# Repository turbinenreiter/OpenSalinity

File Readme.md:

# OpenSalinity

doc - Latex files for the semester thesis  
src - source code  
data - all data gathered during experiments  
hardware - hardware design files  

## Software

The software for the microcontroller is developed using [MicroPython](micropython.org). The controller has to be flashed with the MicroPython firmware before it is able to run the Python scripts. Those Python scripts can be deployed on the microcontroller by copying them over to its filesystem which is present as flash drive when connected to a PC.  

The OpenSalinityGUI offers a simple user interface to capture and visualize data.  

The OpenSalintyCLI shell script uses standard command line tools to do the same.  

DataPlot contains Python scripts to plot and analyze the gathered data.  
All software is licensed under the MIT-license.

## Hardware

In this project, the [Espruino Pico](espruino.com) development board was used, but other boards running MicroPython can replace it.  

Design files for the [MinieC](sparkyswidgets.com) and carrier board files are provided in the [eagle](cadsoft.io)-format.  

Gerbers for the electrode design are offerd as well.  
All hardware is licensed as CC-BY-SA-4.0

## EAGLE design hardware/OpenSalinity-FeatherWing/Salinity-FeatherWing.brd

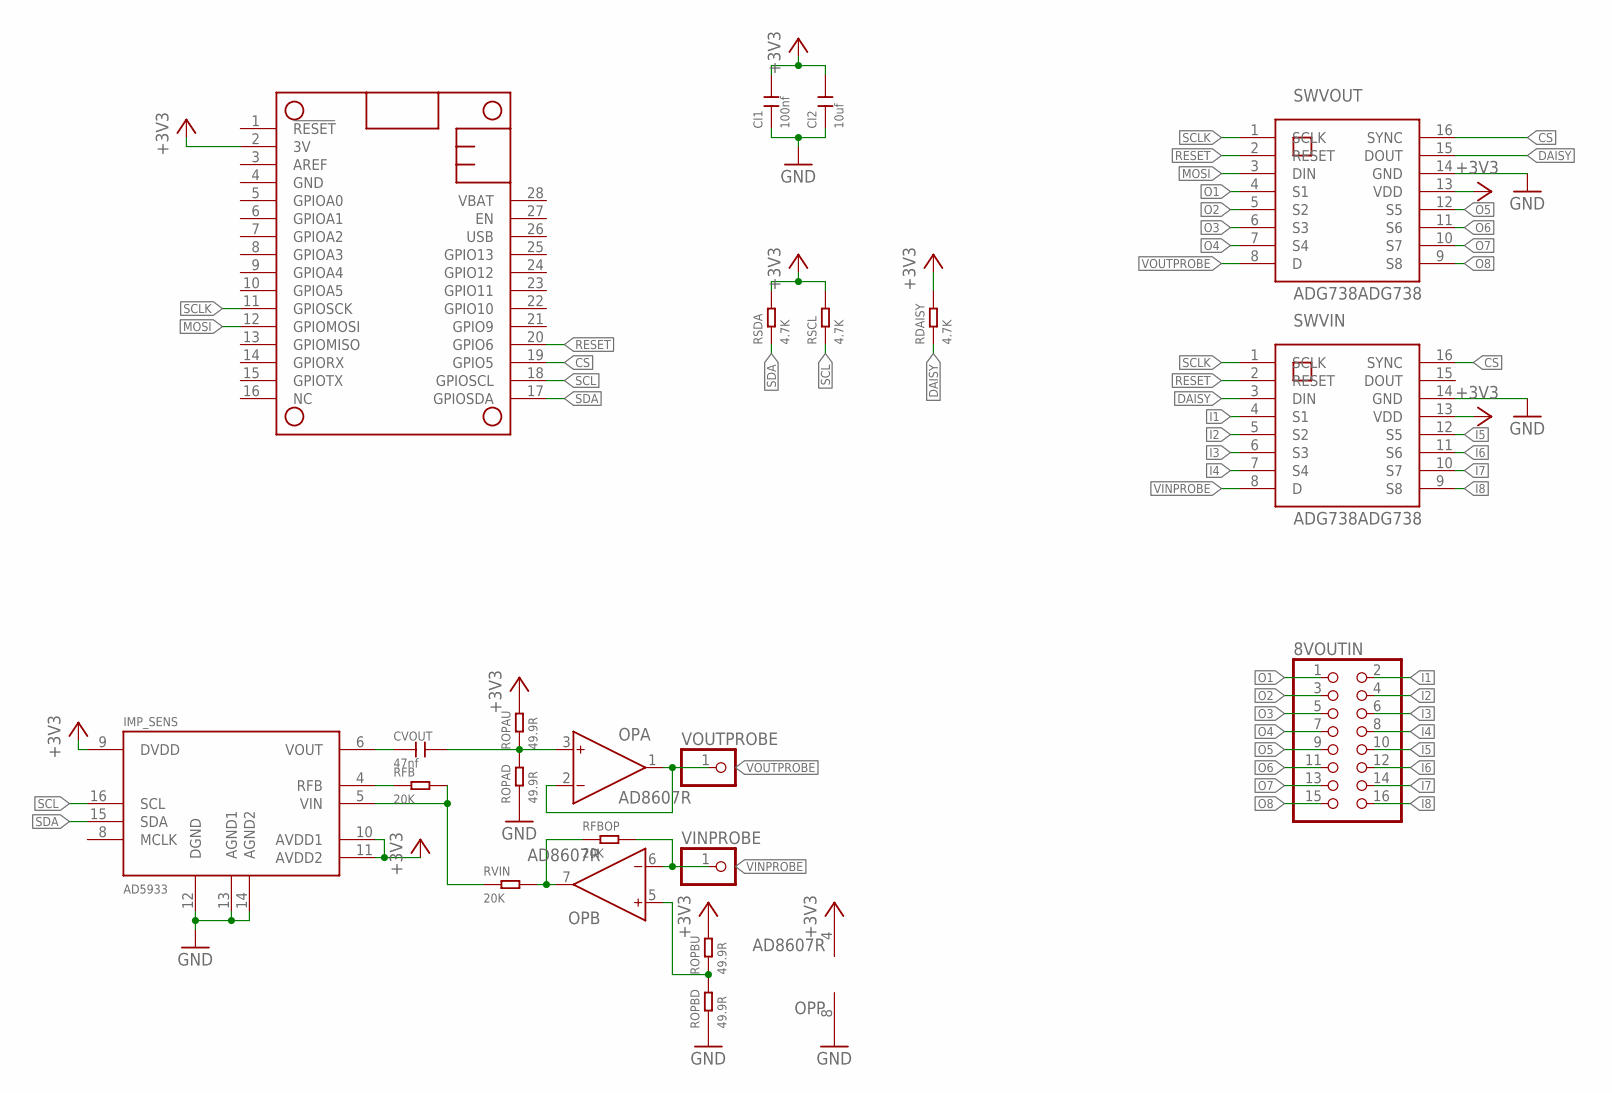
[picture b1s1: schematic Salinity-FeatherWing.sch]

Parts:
8VOUTIN: PINHD-2X8/90; 2X08/90
CI1: 100nf; C0603
CI2: 10uf; C0603
CVOUT: 47nf; C0402
IMP_SENS: AD5933; SSOP16
MS1: FEATHERWING
OP: AD8607R; SO8
RDAISY: 4.7K; R0603
RFB: 20K; R0603
RFBOP: 20K; R0603
ROPAD: 49.9R; R0603
ROPAU: 49.9R; R0603
ROPBD: 49.9R; R0603
ROPBU: 49.9R; R0603
RSCL: 4.7K; R0603
RSDA: 4.7K; R0603
RVIN: 20K; R0603
SWVIN: ADG738ADG738; TSSOP16
SWVOUT: ADG738ADG738; TSSOP16
VINPROBE: PINHD-1X1; 1X01
VOUTPROBE: PINHD-1X1; 1X01

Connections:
+3V3: CI1.2, CI2.2, IMP_SENS.9 (DVDD), IMP_SENS.10 (AVDD1), IMP_SENS.11 (AVDD2), MS1.2 (3V), OP.4 (V-), RDAISY.2, ROPAU.2, ROPBU.2, RSCL.2, RSDA.2, SWVIN.13 (VDD), SWVOUT.13 (VDD)
CS: MS1.19 (GPIO5), SWVIN.16 (SYNC), SWVOUT.16 (SYNC)
DAISY: RDAISY.1, SWVIN.3 (DIN), SWVOUT.15 (DOUT)
GND: CI1.1, CI2.1, IMP_SENS.12 (DGND), IMP_SENS.13 (AGND1), IMP_SENS.14 (AGND2), MS1.4 (GND), OP.8 (V+), ROPAD.1, ROPBD.1, SWVIN.14 (GND), SWVOUT.14 (GND)
I1: 8VOUTIN.2, SWVIN.4 (S1)
I2: 8VOUTIN.4, SWVIN.5 (S2)
I3: 8VOUTIN.6, SWVIN.6 (S3)
I4: 8VOUTIN.8, SWVIN.7 (S4)
I5: 8VOUTIN.10, SWVIN.12 (S5)
I6: 8VOUTIN.12, SWVIN.11 (S6)
I7: 8VOUTIN.14, SWVIN.10 (S7)
I8: 8VOUTIN.16, SWVIN.9 (S8)
MOSI: MS1.12 (GPIOMOSI), SWVOUT.3 (DIN)
unnamed: OP.7 (OUT), RFBOP.1, RVIN.2
unnamed: IMP_SENS.4 (RFB), RFB.1
unnamed: IMP_SENS.5 (VIN), RFB.2, RVIN.1
unnamed: CVOUT.1, IMP_SENS.6 (VOUT)
O1: 8VOUTIN.1, SWVOUT.4 (S1)
O2: 8VOUTIN.3, SWVOUT.5 (S2)
O3: 8VOUTIN.5, SWVOUT.6 (S3)
O4: 8VOUTIN.7, SWVOUT.7 (S4)
O5: 8VOUTIN.9, SWVOUT.12 (S5)
O6: 8VOUTIN.11, SWVOUT.11 (S6)
O7: 8VOUTIN.13, SWVOUT.10 (S7)
O8: 8VOUTIN.15, SWVOUT.9 (S8)
OPA+: CVOUT.2, OP.3 (IN+), ROPAD.2, ROPAU.1
OPB+: OP.5 (IN+), ROPBD.2, ROPBU.1
RESET: MS1.20 (GPIO6), SWVIN.2 (RESET), SWVOUT.2 (RESET)
SCL: IMP_SENS.16 (SCL), MS1.18 (GPIOSCL), RSCL.1
SCLK: MS1.11 (GPIOSCK), SWVIN.1 (SCLK), SWVOUT.1 (SCLK)
SDA: IMP_SENS.15 (SDA), MS1.17 (GPIOSDA), RSDA.1
VINPROBE: OP.6 (IN-), RFBOP.2, SWVIN.8 (D), VINPROBE.1
VOUTPROBE: OP.1 (OUT), OP.2 (IN-), SWVOUT.8 (D), VOUTPROBE.1

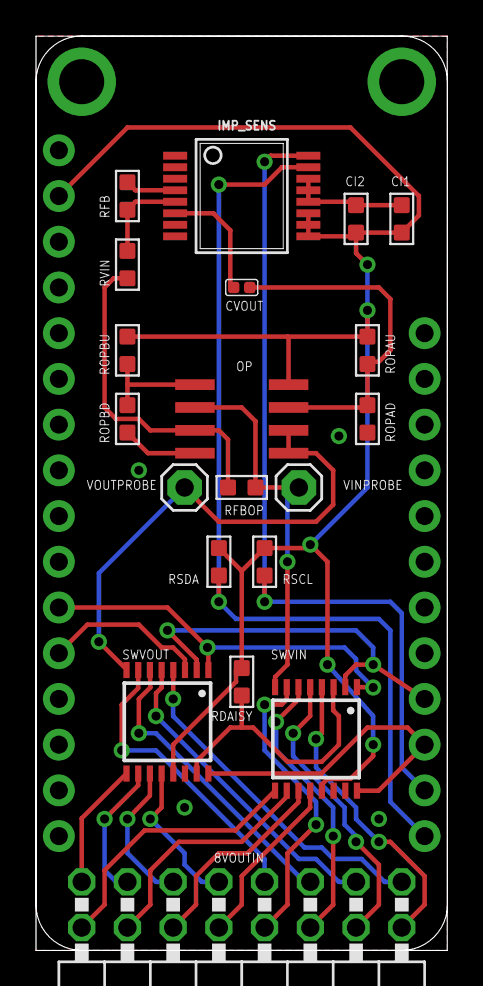
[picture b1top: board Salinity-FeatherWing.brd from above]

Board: 2 copper layers, 22.9 x 50.8 mm, 21 parts (0 on the bottom side), 33 nets.

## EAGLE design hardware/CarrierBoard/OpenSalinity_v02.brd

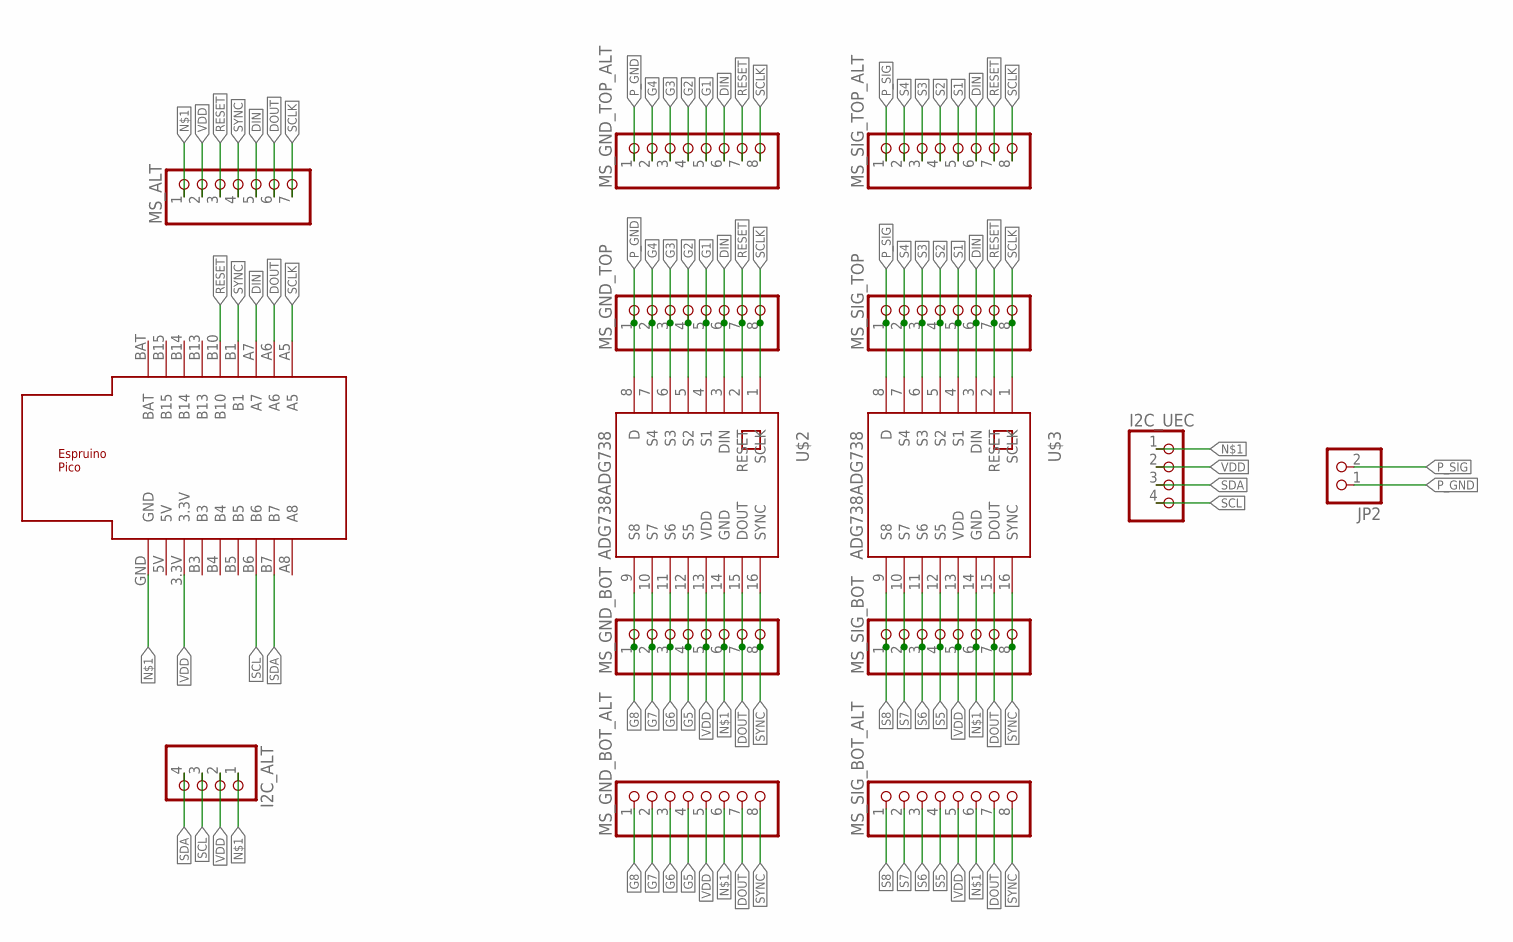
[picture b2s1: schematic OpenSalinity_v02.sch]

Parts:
I2C_ALT, I2C_UEC: PINHD-1X4; 1X04
JP2: PINHD-1X2; 1X02
MS_ALT: PINHD-1X7; 1X07
MS_GND_BOT: PINHD-1X8; 1X08
MS_GND_BOT_ALT: PINHD-1X8; 1X08
MS_GND_TOP: PINHD-1X8; 1X08
MS_GND_TOP_ALT: PINHD-1X8; 1X08
MS_SIG_BOT: PINHD-1X8; 1X08
MS_SIG_BOT_ALT: PINHD-1X8; 1X08
MS_SIG_TOP: PINHD-1X8; 1X08
MS_SIG_TOP_ALT: PINHD-1X8; 1X08
U$1: ESPRUINO_PICO_0.1
U$2, U$3: ADG738ADG738; TSSOP16

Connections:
DIN: MS_ALT.5, MS_GND_TOP.6, MS_GND_TOP_ALT.6, MS_SIG_TOP.6, MS_SIG_TOP_ALT.6, U$1.A7, U$2.3 (DIN), U$3.3 (DIN)
DOUT: MS_ALT.6, MS_GND_BOT.7, MS_GND_BOT_ALT.7, MS_SIG_BOT.7, MS_SIG_BOT_ALT.7, U$1.A6, U$2.15 (DOUT), U$3.15 (DOUT)
G1: MS_GND_TOP.5, MS_GND_TOP_ALT.5, U$2.4 (S1)
G2: MS_GND_TOP.4, MS_GND_TOP_ALT.4, U$2.5 (S2)
G3: MS_GND_TOP.3, MS_GND_TOP_ALT.3, U$2.6 (S3)
G4: MS_GND_TOP.2, MS_GND_TOP_ALT.2, U$2.7 (S4)
G5: MS_GND_BOT.4, MS_GND_BOT_ALT.4, U$2.12 (S5)
G6: MS_GND_BOT.3, MS_GND_BOT_ALT.3, U$2.11 (S6)
G7: MS_GND_BOT.2, MS_GND_BOT_ALT.2, U$2.10 (S7)
G8: MS_GND_BOT.1, MS_GND_BOT_ALT.1, U$2.9 (S8)
unnamed: I2C_ALT.1, I2C_UEC.1, MS_ALT.1, MS_GND_BOT.6, MS_GND_BOT_ALT.6, MS_SIG_BOT.6, MS_SIG_BOT_ALT.6, U$1.GND, U$2.14 (GND), U$3.14 (GND)
P_GND: JP2.1, MS_GND_TOP.1, MS_GND_TOP_ALT.1, U$2.8 (D)
P_SIG: JP2.2, MS_SIG_TOP.1, MS_SIG_TOP_ALT.1, U$3.8 (D)
RESET: MS_ALT.3, MS_GND_TOP.7, MS_GND_TOP_ALT.7, MS_SIG_TOP.7, MS_SIG_TOP_ALT.7, U$1.B10, U$2.2 (RESET), U$3.2 (RESET)
S1: MS_SIG_TOP.5, MS_SIG_TOP_ALT.5, U$3.4 (S1)
S2: MS_SIG_TOP.4, MS_SIG_TOP_ALT.4, U$3.5 (S2)
S3: MS_SIG_TOP.3, MS_SIG_TOP_ALT.3, U$3.6 (S3)
S4: MS_SIG_TOP.2, MS_SIG_TOP_ALT.2, U$3.7 (S4)
S5: MS_SIG_BOT.4, MS_SIG_BOT_ALT.4, U$3.12 (S5)
S6: MS_SIG_BOT.3, MS_SIG_BOT_ALT.3, U$3.11 (S6)
S7: MS_SIG_BOT.2, MS_SIG_BOT_ALT.2, U$3.10 (S7)
S8: MS_SIG_BOT.1, MS_SIG_BOT_ALT.1, U$3.9 (S8)
SCL: I2C_ALT.3, I2C_UEC.4, U$1.B6
SCLK: MS_ALT.7, MS_GND_TOP.8, MS_GND_TOP_ALT.8, MS_SIG_TOP.8, MS_SIG_TOP_ALT.8, U$1.A5, U$2.1 (SCLK), U$3.1 (SCLK)
SDA: I2C_ALT.4, I2C_UEC.3, U$1.B7
SYNC: MS_ALT.4, MS_GND_BOT.8, MS_GND_BOT_ALT.8, MS_SIG_BOT.8, MS_SIG_BOT_ALT.8, U$1.B1, U$2.16 (SYNC), U$3.16 (SYNC)
VDD: I2C_ALT.2, I2C_UEC.2, MS_ALT.2, MS_GND_BOT.5, MS_GND_BOT_ALT.5, MS_SIG_BOT.5, MS_SIG_BOT_ALT.5, U$1.3.3V, U$2.13 (VDD), U$3.13 (VDD)

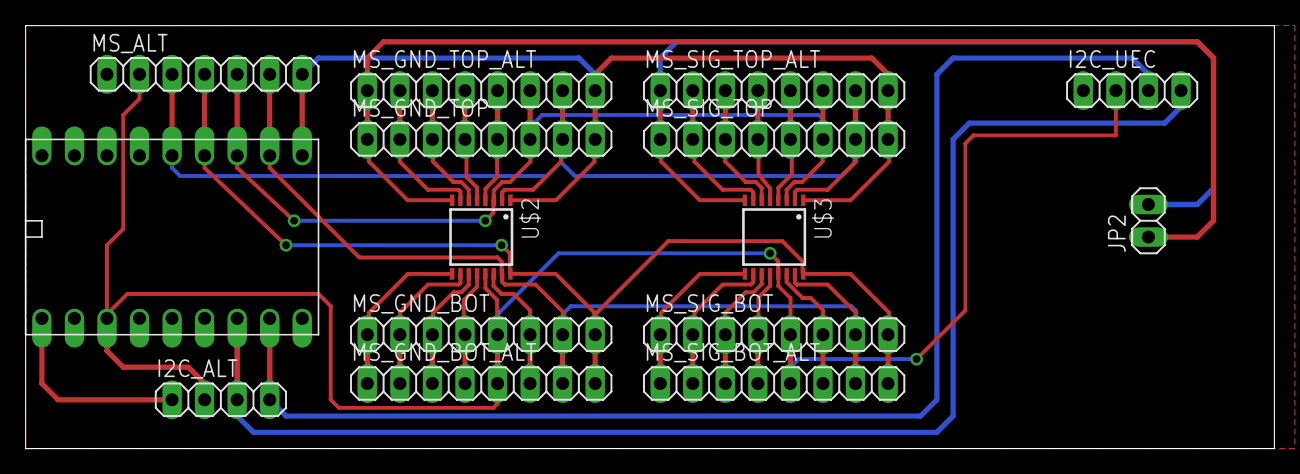
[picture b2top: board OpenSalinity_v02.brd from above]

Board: 2 copper layers, 97.5 x 33.0 mm, 15 parts (0 on the bottom side), 27 nets.

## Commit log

2016-07-04 init
2016-07-05 new intro
2016-07-11 new data, new vis
2016-07-19 little progress
2016-07-19 added Readme.md
2016-07-20 modified objectives, extended background
2016-07-24 prefinished intro/obj/background
2016-07-25 retouched
2016-07-25 wrote sensor/matrixswitch
2016-07-26 wrote miniec
2016-07-27 finished GUI
2016-07-28 doc GUI
2016-07-30 design almost done
2016-07-30 added data conditioning figure
2016-07-30 implemented feedback
2016-08-05 ver:res, src:tau
2016-08-05 bom, fixes, deployability
2016-08-05 fig sysdesign added color and text
2016-08-05 fig text expand
2016-08-06 sens and range
2016-08-06 fixes
2016-08-07 getting there
2016-08-07 when whill it end
2016-08-08 almost there
2016-08-08 almost done
2016-08-09 spelling fixes
2016-08-09 more fixes
2016-08-10 almost final
2016-08-10 clean up
2016-08-11 really almost done
2016-08-11 final push
2016-08-11 readme
2016-08-12 fixed typo in main.py
2016-08-21 added presentation template
2016-08-22 started presentation
2016-08-23 presentation halfway done
2016-08-23 added new hardware
2016-08-26 presentation v0.9
2016-08-29 final presentation
2017-03-07 Add smart I2C device detection to avoid errors when switching ADCs
2017-03-07 Fix typo in dir name

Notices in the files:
hardware/CarrierBoard/OpenSalinity_v02.sch:
CNAME: CC BY SA 4.0
parts and their libraries:
SparkFun-Aesthetics: Licensing: Creative Commons ShareAlike 4.0 International - https://creativecommons.org/licenses/by-sa/4.0
